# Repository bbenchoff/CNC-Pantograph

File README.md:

CNC-Pantograph
==============

A pantograph for distributing power along a makerslide rail

A small experiment for a possible upcoming project. Is meant to be one part of a system that distributes power along an aluminum extrusion for CNC and robotics work. Think of it as a model train track, but with CNC stuff.

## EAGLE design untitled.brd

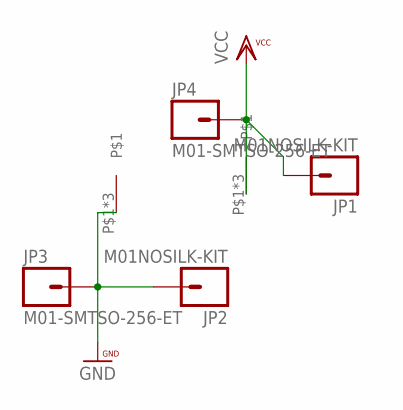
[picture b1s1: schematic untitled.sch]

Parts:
JP1, JP2: M01NOSILK-KIT; 1X01NS-KIT
JP3, JP4: M01-SMTSO-256-ET; SMTSO-256-ET
U$1, U$2: PANTOGRAPH; WIREHOLDER

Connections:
GND: JP2.1, JP3.P$1, U$1.P$1, U$1.P$2, U$1.P$3
VCC: JP1.1, JP4.P$1, U$2.P$1, U$2.P$2, U$2.P$3

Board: 2 copper layers, 6 parts (0 on the bottom side), 2 nets, no tracks yet.

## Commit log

2014-08-31 :circus_tent: Added .gitattributes & .gitignore files
2014-08-31 First commit
    Added board and gerbers

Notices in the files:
parts and their libraries:
SparkFun-Connectors: Licensing: CC v3.0 Share-Alike You are welcome to use this library for commercial purposes.
PatternAgents-Beautify: License : http://creativecommons.org/licenses/by-sa/3.0
(Creative Commons 3.0)
